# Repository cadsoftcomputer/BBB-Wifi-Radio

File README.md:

# BBB-Wifi-Radio
Internet Radio based on the Beaglebone Black platform made by Jorge Garcia

This repository contains the hardware and software files I created in order to make a Wifi Radio using the Beaglebone Black
single board computer.

This Radio use a Python-Tkinter interface to communicate with MPC and MPD in order to play internet radio stations. In th
various folders you will find further information about what each of the files contains and what their purpose is in the
scheme of the project.

If you have any questions please feel free to contact me, jorge@cadsoftusa.com or call 954-237-0932.

I would like to extend a special thanks to Shabaz from the Element14 community and Robert C Nelson, William Hermans,
Peter Gregory from the Beagleboard Groups forum, and Dr. Derek Molloy author of Exploring Beaglebone . Without their help and insight this project would never have been completed.

Here are links to the resources used in developing this project, I tried to organize them as best as I could

Inspiration
* http://mightyohm.com/blog/2008/10/building-a-wifi-radio-part-1-introduction/

Setting up MPC and MPD
* http://crunchbang.org/forums/viewtopic.php?pid=182574

Audio Cape Design
* http://www.element14.com/community/community/designcenter/single-board-computers/next-gen_beaglebone/blog/2013/05/28/bbb--audio-notes
* http://www.element14.com/community/community/designcenter/single-board-computers/next-gen_beaglebone/blog/2013/07/06/bbb--building-a-dac

BeagleBoard Forum
* https://groups.google.com/forum/#!forum/beagleboard

Device Tree Overlay Info
* http://derekmolloy.ie/gpios-on-the-beaglebone-black-using-device-tree-overlays/
* http://elinux.org/BeagleBone_and_the_3.8_Kernel
* https://github.com/beagleboard/linux/blob/3.8/firmware/capes/cape-boneblack-hdmi-00A0.dts

Python
* https://www.python.org/
* http://www.diveintopython3.net/

Tkinter References
* http://www.tkdocs.com/
* http://infohost.nmt.edu/tcc/help/pubs/tkinter/web/index.html

LXDE 
* https://wiki.archlinux.org/index.php/LXDE#Autostart_Programs

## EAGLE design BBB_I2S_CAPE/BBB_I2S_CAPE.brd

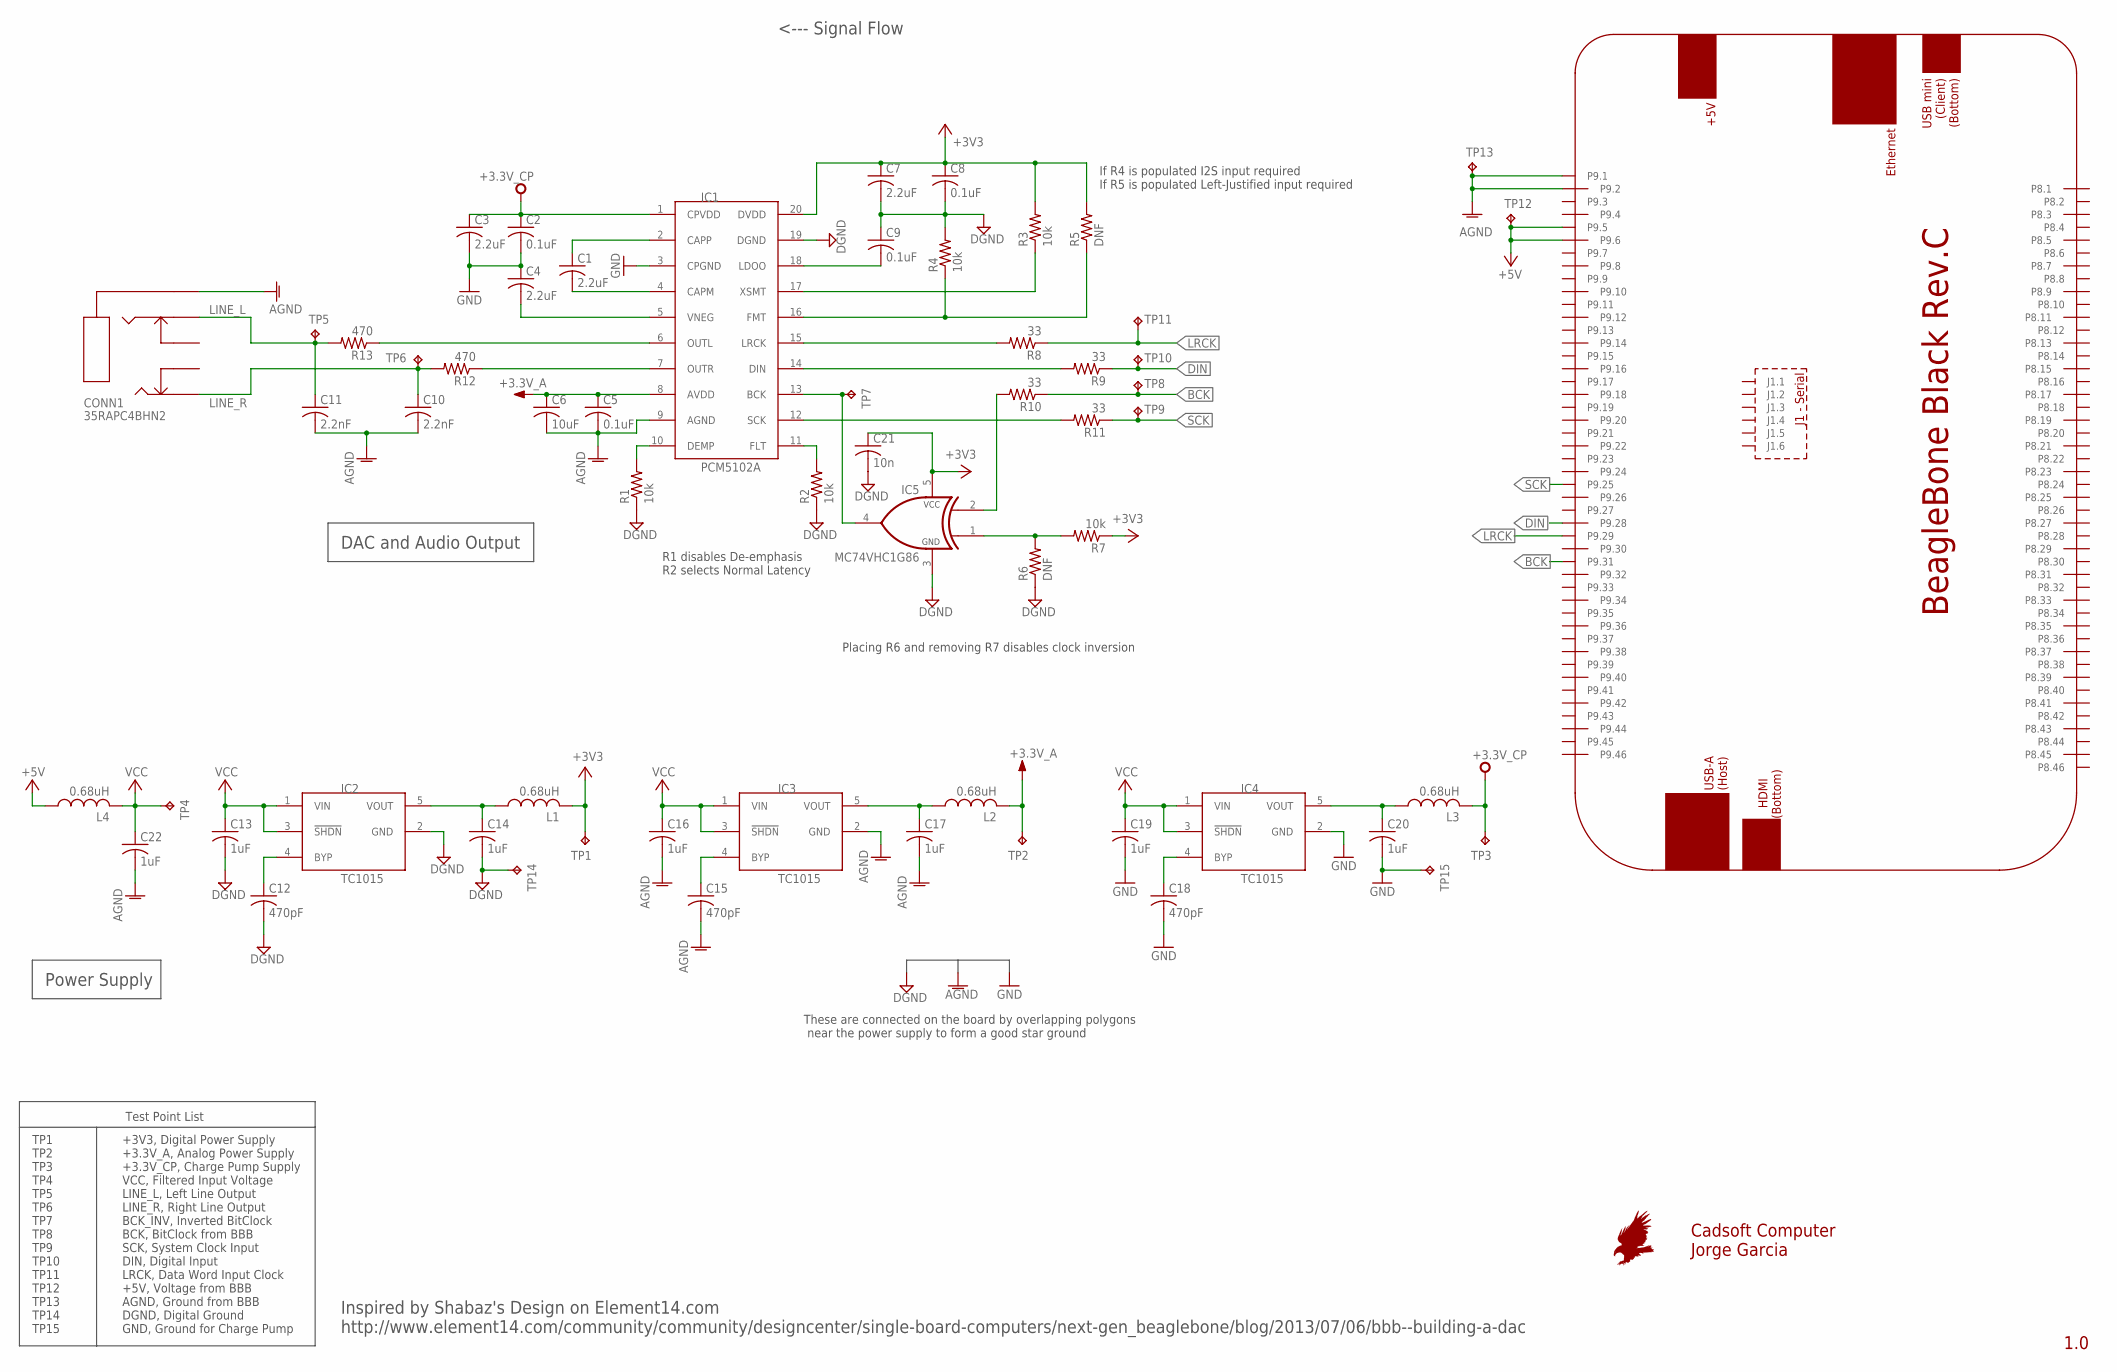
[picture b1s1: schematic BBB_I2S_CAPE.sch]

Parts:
C1, C3, C4, C7: 2.2uF; C0805; MPN GCM21BR71C225KA64L
C2, C5, C8, C9: 0.1uF; C0805; MPN VJ0805Y104KXAMT
C6: 10uF; C0805; MPN 08053D106KAT2A
C10, C11: 2.2nF; C0805; MPN 08055C222KAT2A
C12, C15, C18: 470pF; C0805; MPN MC0805B471K500CT
C13, C14, C16, C17, C19, C20, C22: 1uF; C0805; MPN C0805X105K3RACAUTO
C21: 10n; C0805; MPN MC0805B103K500CT
CONN1: 35RAPC4BHN2; MPN 35RAPC4BHN2
IC1: PCM5102A; TSSOP20; MPN PCM5102AQPWRQ1
IC2, IC3, IC4: TC1015; SOT23-5L; MPN TC1015-3.3VCT713
IC5: MC74VHC1G86; SOT23-5L; MPN SN74AHC1G86DBVR
L1, L2, L3, L4: 0.68uH; R0805; MPN MCFT000156
PCB1: BEAGLEBONE_BLACK_CAPE
R1, R2, R3, R4, R7: 10k; R0805; MPN MCTC0525B1002T5E
R5, R6: DNF; R0805
R8, R9, R10, R11: 33; R0805; MPN CR0805-JW-330ELF
R12, R13: 470; R0805; MPN ERA-6AEB471V
TP1, TP2, TP3, TP4, TP5, TP6, TP7, TP8, TP9, TP10, TP11, TP12, TP13, TP14, TP15: TPPAD1-17; P1-17

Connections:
+3.3V_A: C5.1, C6.1, IC1.8 (AVDD), L2.2, TP2.TP
+3.3V_CP: C2.1, C3.1, IC1.1 (CPVDD), L3.2, TP3.TP
+3V3: C7.1, C8.1, C21.1, IC1.20 (DVDD), IC5.5 (VCC), L1.2, R3.2, R5.2, R7.1, TP1.TP
+5V: L4.1, PCB1.P9.5, PCB1.P9.6, TP12.TP
AGND: C5.2, C6.2, C10.2, C11.2, C15.2, C16.2, C17.2, C22.2, CONN1.1, IC1.9 (AGND), IC3.2 (GND), PCB1.P9.1, PCB1.P9.2, TP13.TP
BCK: PCB1.P9.31, R10.1, TP8.TP
BCK_INV: IC1.13 (BCK), IC5.4 (OUT), TP7.TP
DGND: C7.2, C8.2, C9.1, C12.2, C13.2, C14.2, C21.2, IC1.19 (DGND), IC2.2 (GND), IC5.3 (GND), R1.1, R2.1, R4.2, R6.1, TP14.TP
DIN: PCB1.P9.28, R9.1, TP10.TP
GND: C2.2, C3.2, C4.1, C18.2, C19.2, C20.2, IC1.3 (CPGND), IC4.2 (GND), TP15.TP
LINE_L: C11.1, CONN1.3, R13.2, TP5.TP
LINE_R: C10.1, CONN1.2, R12.2, TP6.TP
LRCK: PCB1.P9.29, R8.1, TP11.TP
unnamed: C1.2, IC1.4 (CAPM)
unnamed: C1.1, IC1.2 (CAPP)
unnamed: C4.2, IC1.5 (VNEG)
unnamed: IC1.15 (LRCK), R8.2
unnamed: IC1.17 (XSMT), R3.1
unnamed: IC1.14 (DIN), R9.2
unnamed: IC1.10 (DEMP), R1.2
unnamed: IC1.11 (FLT), R2.2
unnamed: IC5.2 (INA), R10.2
unnamed: C9.2, IC1.18 (LDOO)
unnamed: IC5.1 (INB), R6.2, R7.2
unnamed: IC1.16 (FMT), R4.1, R5.1
unnamed: IC1.12 (SCK), R11.2
unnamed: IC1.7 (OUTR), R12.1
unnamed: IC1.6 (OUTL), R13.1
unnamed: C12.1, IC2.4 (BYP)
unnamed: C14.1, IC2.5 (VOUT), L1.1
unnamed: C15.1, IC3.4 (BYP)
unnamed: C17.1, IC3.5 (VOUT), L2.1
unnamed: C18.1, IC4.4 (BYP)
unnamed: C20.1, IC4.5 (VOUT), L3.1
SCK: PCB1.P9.25, R11.1, TP9.TP
VCC: C13.1, C16.1, C19.1, C22.1, IC2.1 (VIN), IC2.3 (!SHDN), IC3.1 (VIN), IC3.3 (!SHDN), IC4.1 (VIN), IC4.3 (!SHDN), L4.2, TP4.TP

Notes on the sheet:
Placing R6 and removing R7 disables clock inversion
If R4 is populated I2S input required If R5 is populated Left-Justified input required
R1 disables De-emphasis R2 selects Normal Latency
<--- Signal Flow
DAC and Audio Output
Power Supply
These are connected on the board by overlapping polygons near the power supply to form a good star ground
TP1 TP2 TP3 TP4 TP5 TP6 TP7 TP8 TP9 TP10 TP11 TP12 TP13 TP14 TP15
+3V3, Digital Power Supply +3.3V_A, Analog Power Supply +3.3V_CP, Charge Pump Supply VCC, Filtered Input Voltage LINE_L, Left Line Output LINE_R, Right Line Output BCK_INV, Inverted BitClock BCK, BitClock from BBB SCK, System Clock Input DIN, Digital Input LRCK, Data Word Input Clock +5V, Voltage f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
Test Point List
1.0
Cadsoft Computer Jorge Garcia
Inspired by Shabaz's Design on Element14.com http://www.element14.com/community/community/designcenter/single-board-computers/next-gen_beaglebone/blog/2013/07/06/bbb--building-a-dac

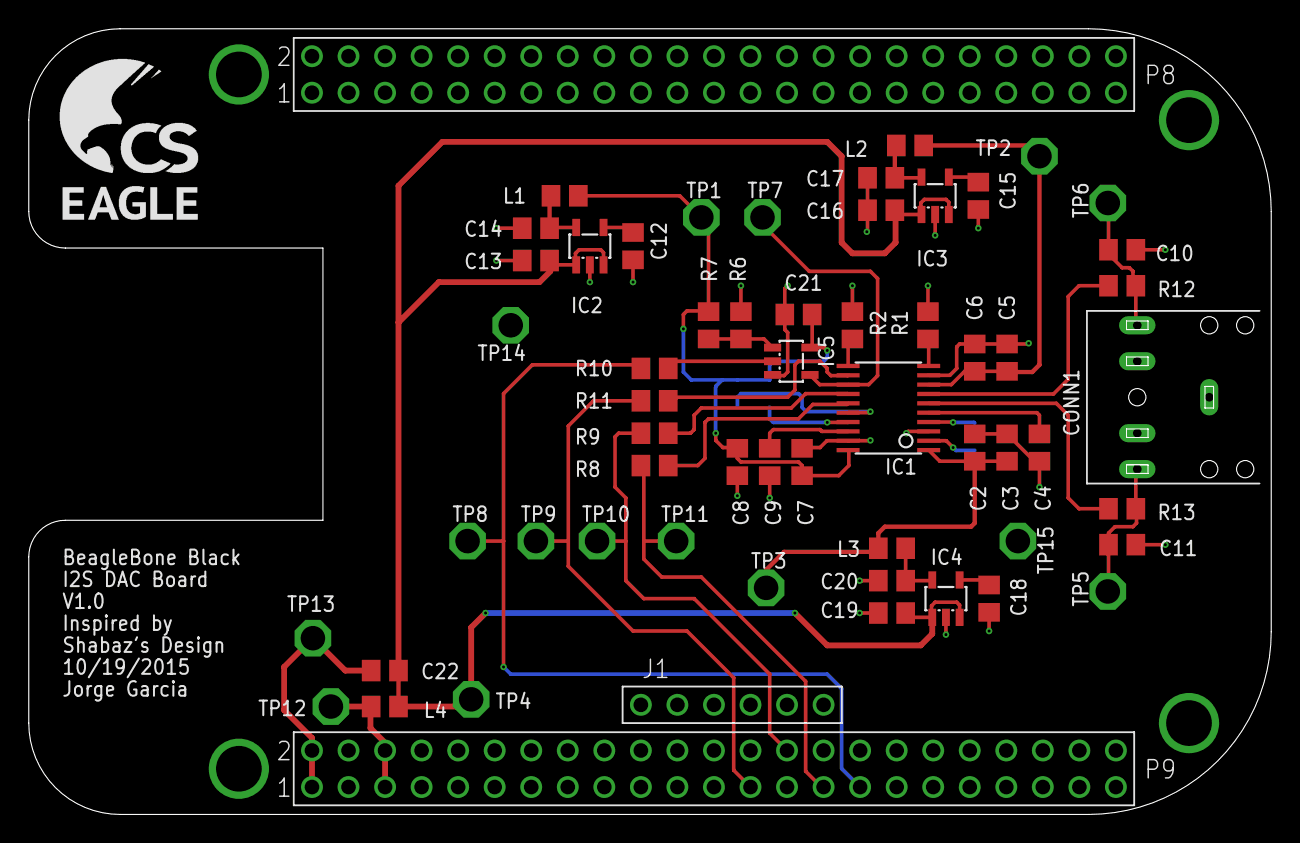
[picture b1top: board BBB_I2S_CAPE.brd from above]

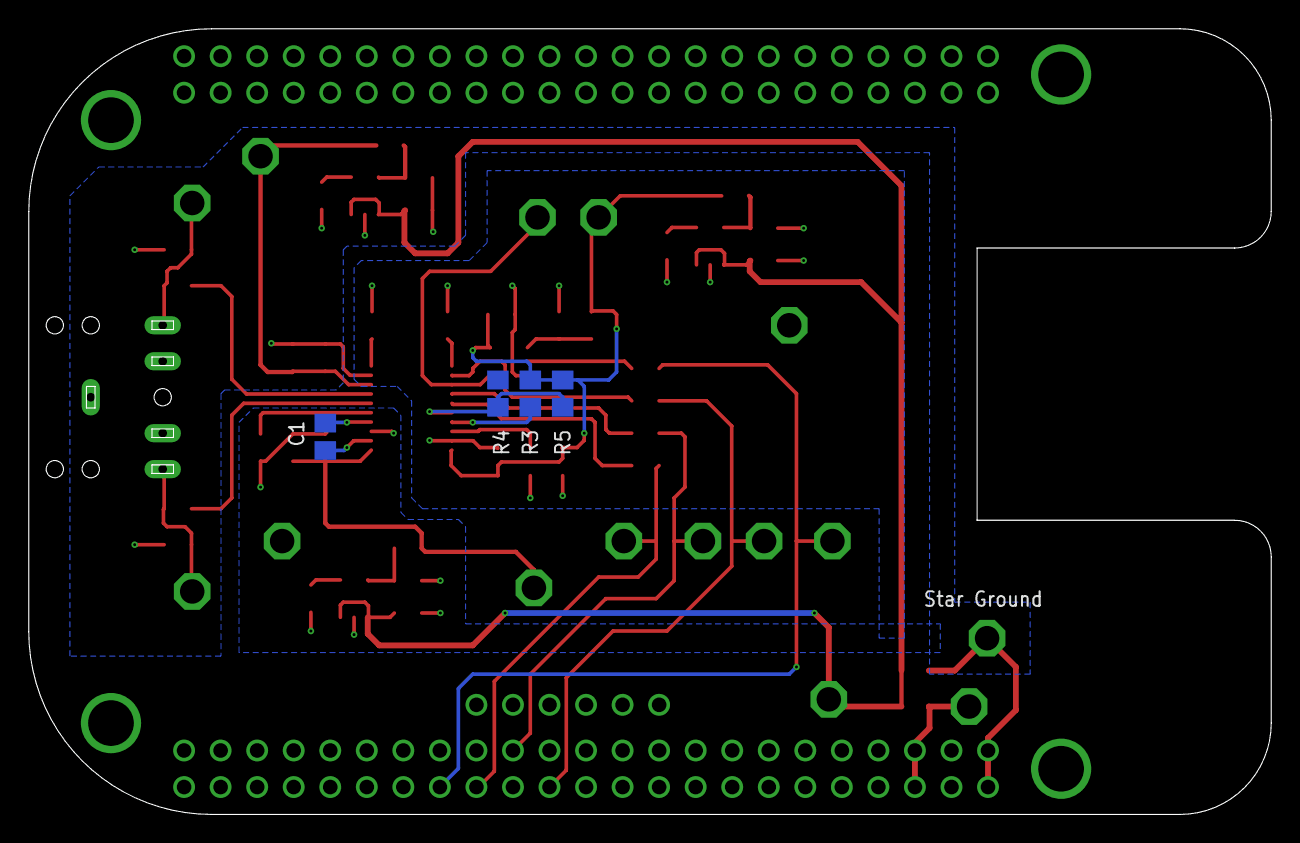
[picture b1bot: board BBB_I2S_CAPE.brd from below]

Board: 2 copper layers, 86.4 x 54.6 mm, 61 parts (4 on the bottom side), 36 nets.

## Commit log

2016-01-06 :confetti_ball: Added .gitattributes & .gitignore files
2016-01-06 1.0 Release of the Beaglebone Black Wifi Radio
    This file contains all of the files for the hardware and software to
    reproduce the Wifi Radio made by Jorge Garcia of Cadsoft Computer
